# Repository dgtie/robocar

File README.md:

# robocar
stm32f103c8t6

## Setup SD card
[Download Raspberry Pi Zero WH image](https://polyuit-my.sharepoint.com/:u:/g/personal/ensylam_polyu_edu_hk/EfPde7mzcR5NiaSuWeZethsBixlZN2U6amez3VQq-VrPfw?e=RhzQuq)\
Write image to SD card. (using balenaEtcher or otherwise)\
Disable SD card reader (through device manager) and then enable it again.\
Modify the following files (in "boot" drive):

- wpa_supplicant.conf (ssid, password)
- hostname & hosts (raspberrypi -> newHostname, eg 19xxxxxxd)

Put SD card to raspberry pi zero and boot.

## SSH to raspberry pi
launch command prompt\
enter "ping -4 19xxxxxxd.local" to check ip address (Bonjour Print Service)\
SSH via putty or otherwise. (ssh pi@19xxxxxxd.local) (pwd = raspberry)

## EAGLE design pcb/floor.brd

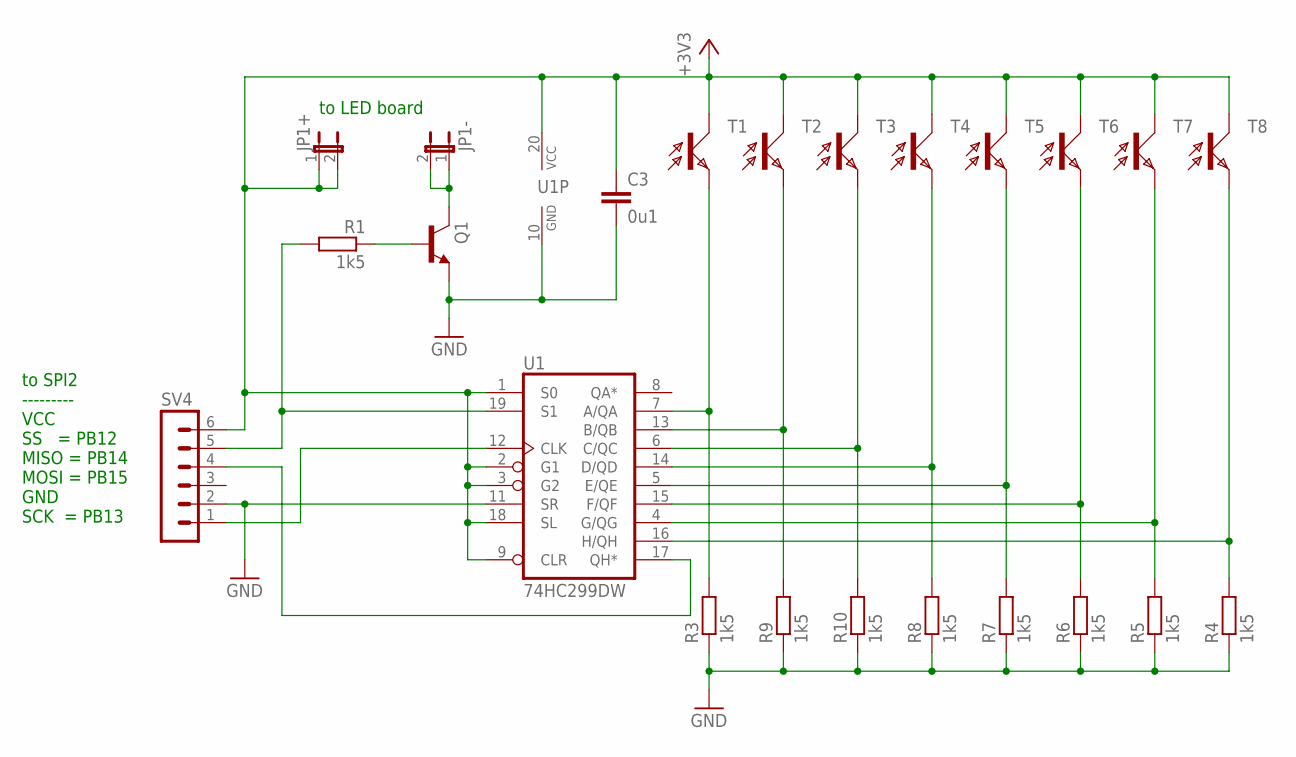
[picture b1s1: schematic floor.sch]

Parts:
C3: 0u1; C0805
JP1+, JP1-: JP1E; JP1
Q1: BC817-25SMD; SOT23-BEC
R1, R3, R4, R5, R6, R7, R8, R9, R10: 1k5; M0805
SV4: MA06-1
T1, T2, T3, T4, T5, T6, T7, T8: PT17-21B; CHIPLED_0805
U1: 74HC299DW; SO20W

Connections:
+3V3: C3.1, JP1+.1, JP1+.2, SV4.6, T1.C, T2.C, T3.C, T4.C, T5.C, T6.C, T7.C, T8.C, U1.1 (S0), U1.2 (G1), U1.3 (G2), U1.9 (CLR), U1.18 (SL), U1.20 (VCC)
GND: C3.2, Q1.E, R3.1, R4.1, R5.1, R6.1, R7.1, R8.1, R9.1, R10.1, SV4.2, U1.10 (GND), U1.11 (SR)
unnamed: R3.2, T1.A (E), U1.7 (A/QA)
unnamed: JP1-.1, JP1-.2, Q1.C
unnamed: R4.2, T8.A (E), U1.16 (H/QH)
unnamed: R9.2, T2.A (E), U1.13 (B/QB)
unnamed: R10.2, T3.A (E), U1.6 (C/QC)
unnamed: R8.2, T4.A (E), U1.14 (D/QD)
unnamed: R7.2, T5.A (E), U1.5 (E/QE)
unnamed: R6.2, T6.A (E), U1.15 (F/QF)
unnamed: R5.2, T7.A (E), U1.4 (G/QG)
unnamed: SV4.1, U1.12 (CLK)
unnamed: SV4.4, U1.17 (QH*)
unnamed: R1.2, SV4.5, U1.19 (S1)
unnamed: Q1.B, R1.1

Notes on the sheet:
to SPI2 --------- VCC SS = PB12 MISO = PB14 MOSI = PB15 GND SCK = PB13
to LED board

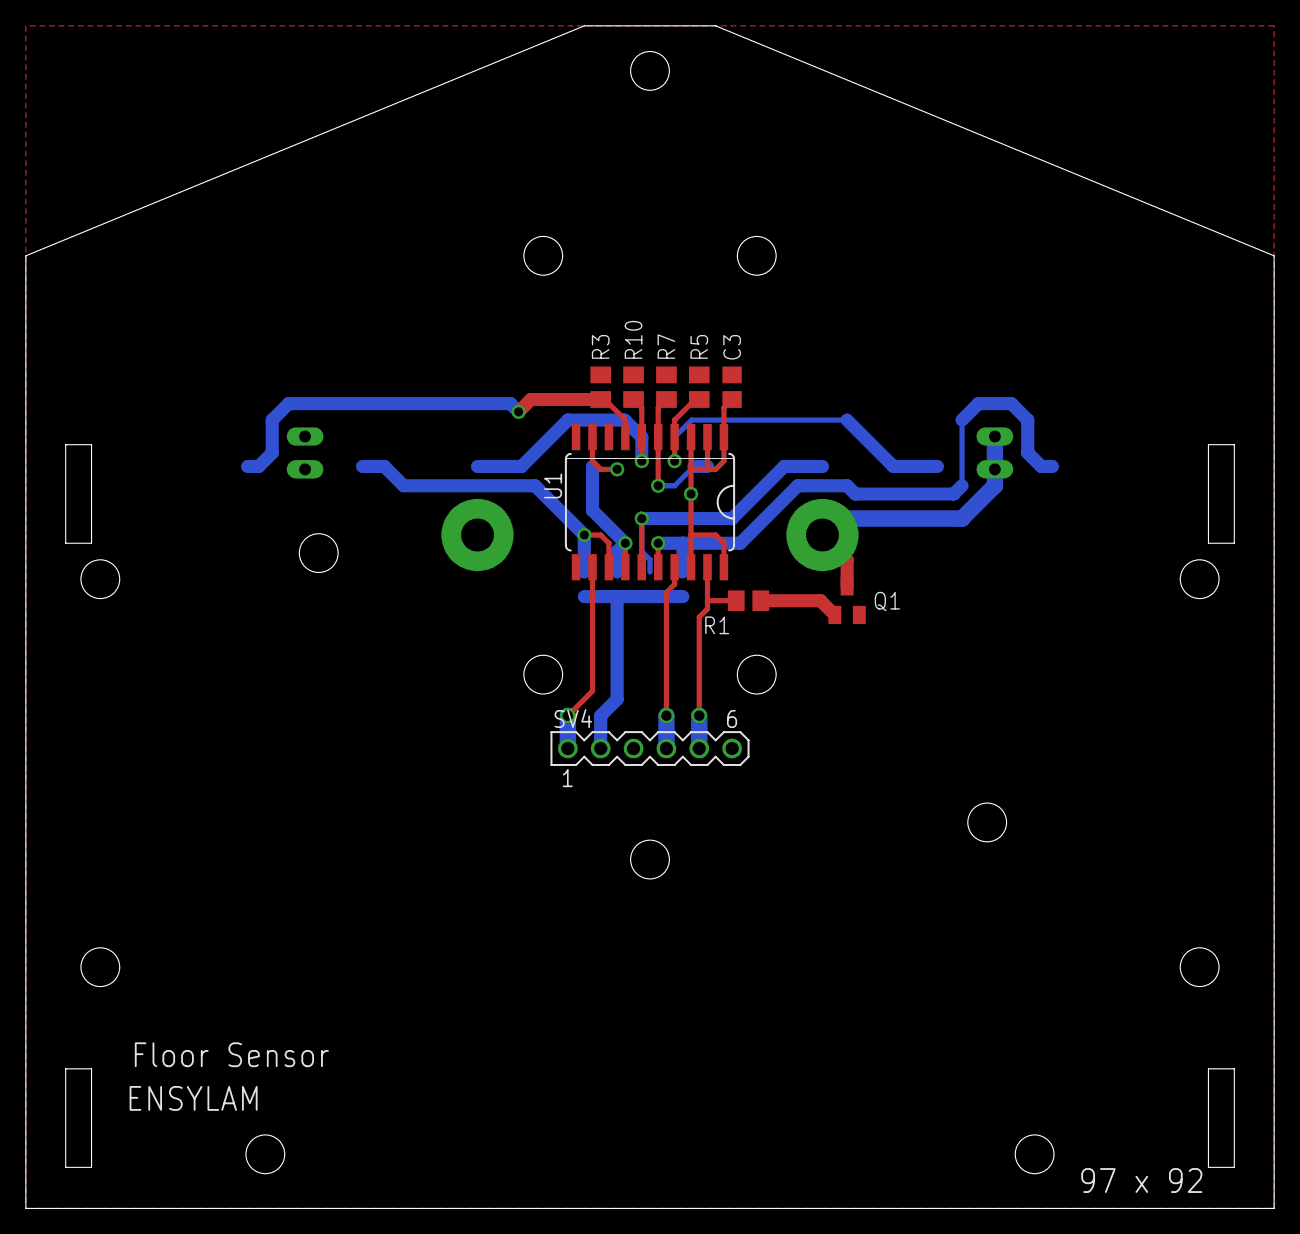
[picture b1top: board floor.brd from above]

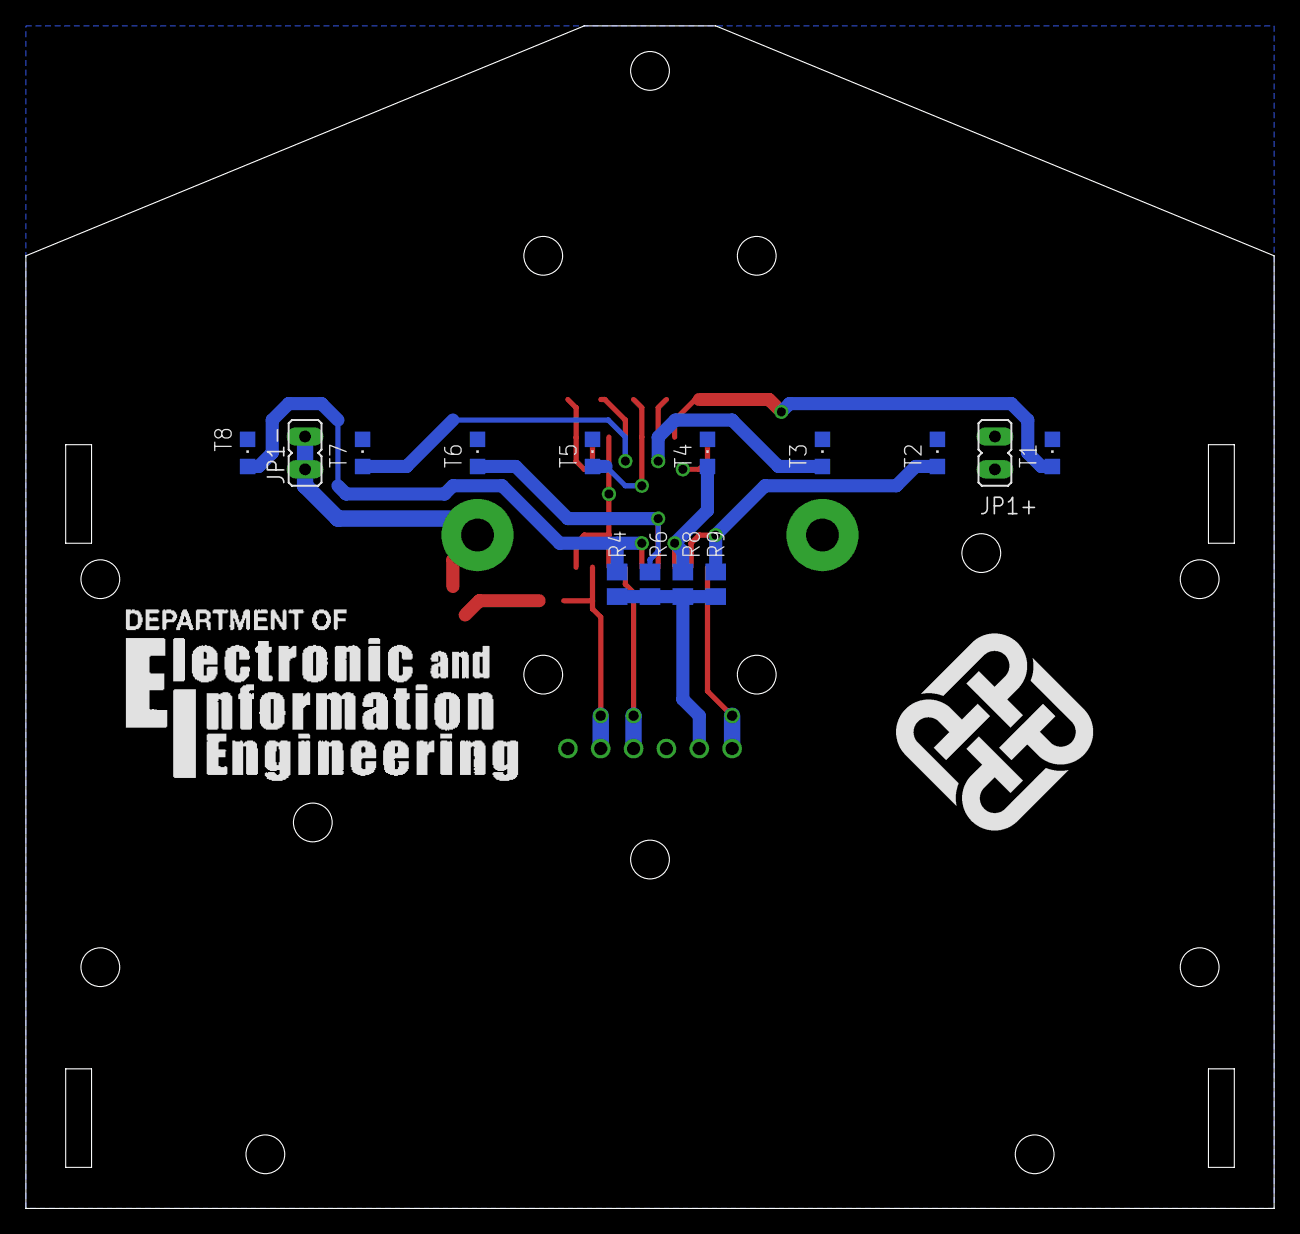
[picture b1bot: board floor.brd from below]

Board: 2 copper layers, 96.5 x 91.4 mm, 25 parts (16 on the bottom side), 15 nets.

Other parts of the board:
U$1: EIE
U$2: POLYU

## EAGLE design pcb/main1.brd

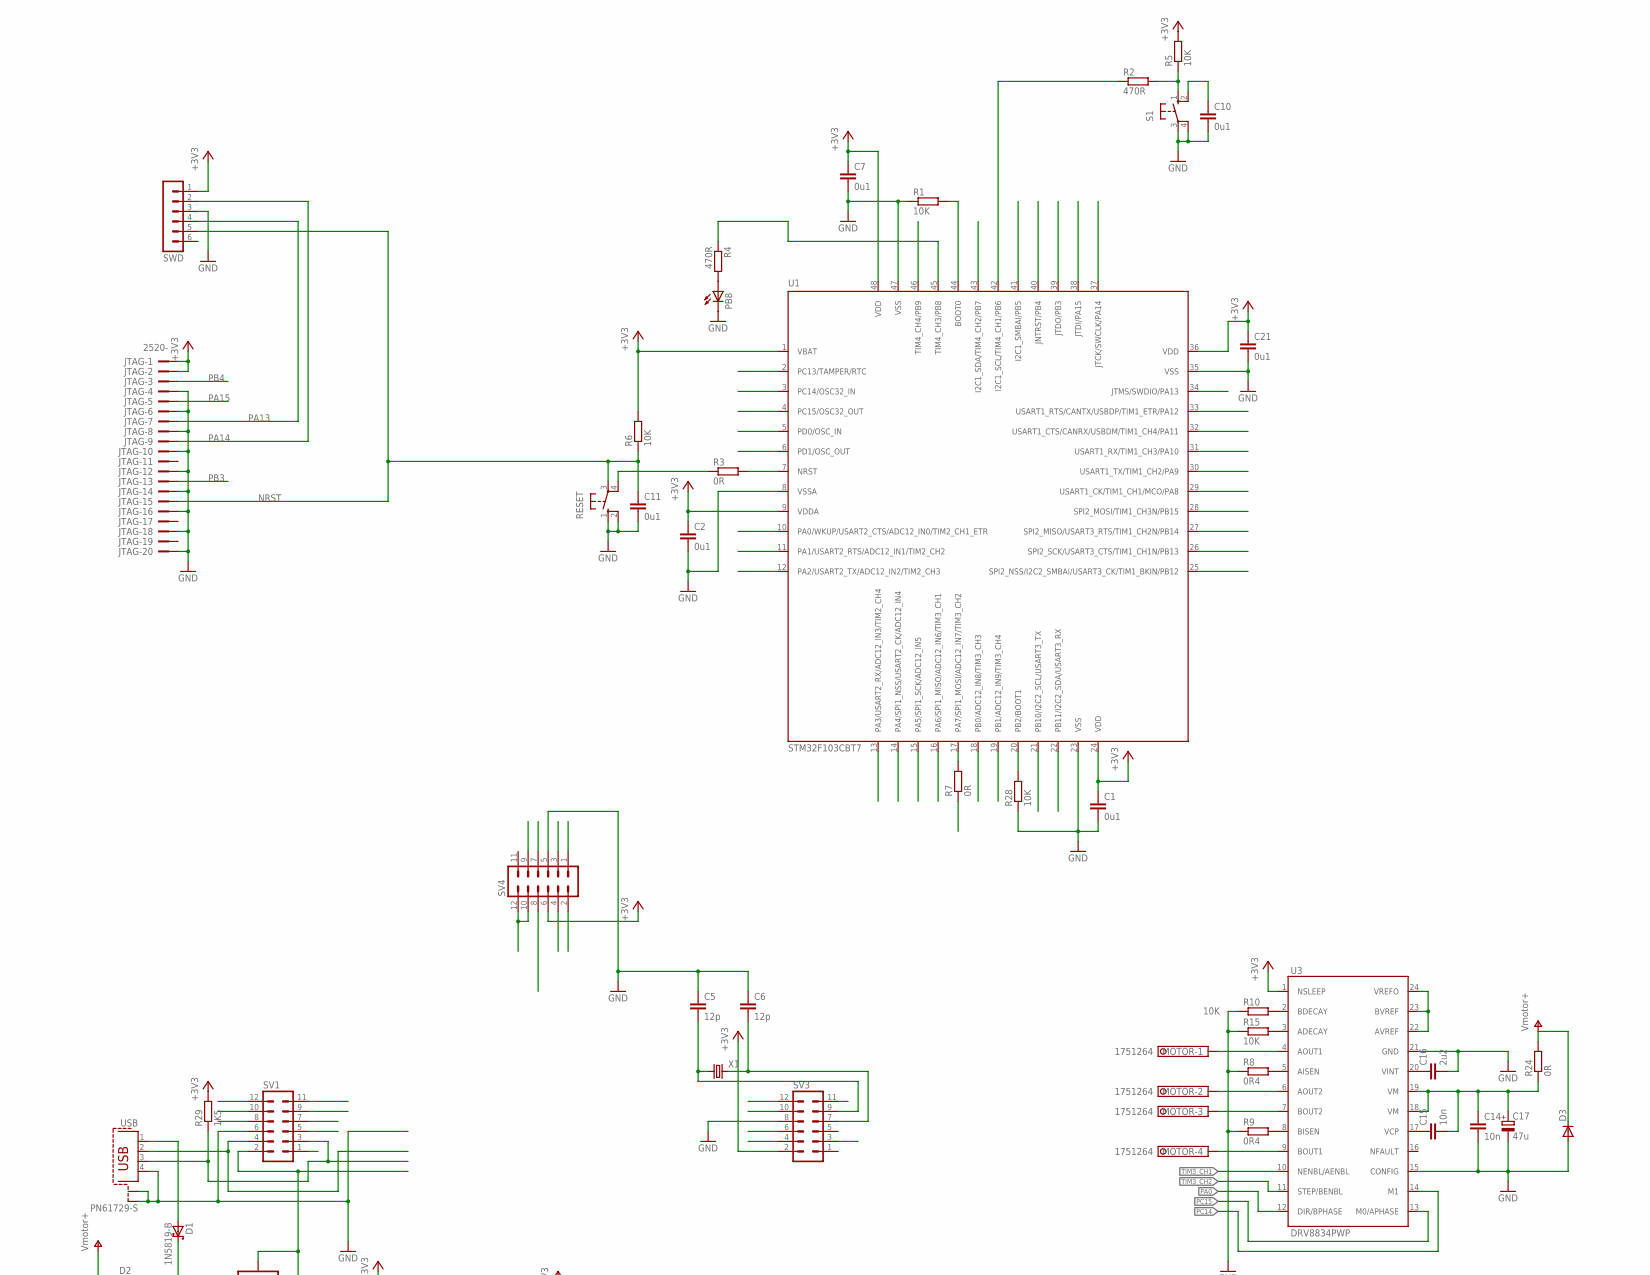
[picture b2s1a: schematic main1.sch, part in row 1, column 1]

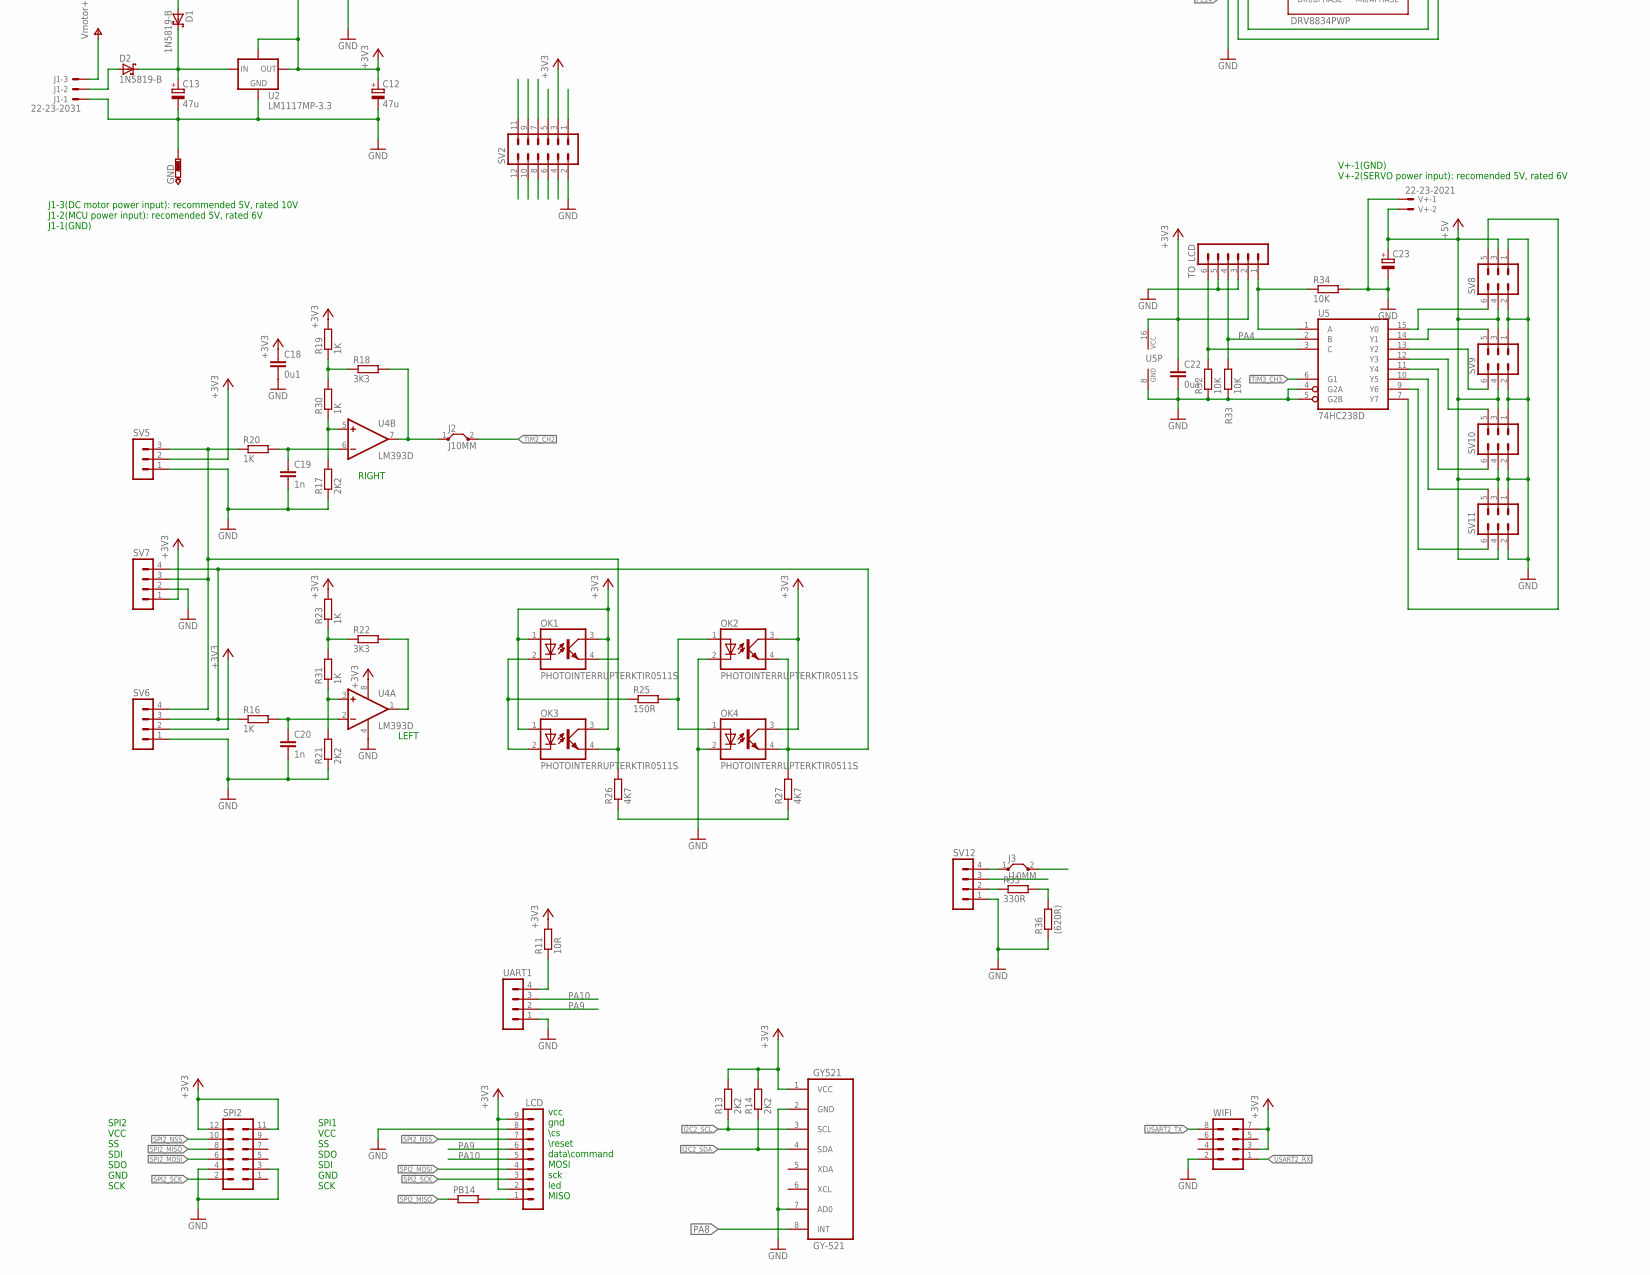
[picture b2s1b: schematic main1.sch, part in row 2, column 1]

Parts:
C1, C2, C7, C10, C11, C18, C21, C22: 0u1; C0805
C5, C6: 12p; C0805
C12, C13, C17: 47u; E1,8-4
C14, C15: 10n; C0805
C16: 2u2; C0805
C19, C20: 1n; C0805
C23: CPOL-EUE2.5-7; E2,5-7
D1, D2: 1N5819-B; DO41-7.6
D3: DIODE-SMB; SMB
GND: PTR1PAD1-13; P1-13
GY521: GY-521
J1: 22-23-2031
J2, J3: J10MM; 10
JTAG: 2520-; PAK100/2500-20
LCD: MA09-1
MOTOR: 1751264
OK1, OK2, OK3, OK4: PHOTOINTERRUPTERKTIR0511S; KTIR0511S
PB8: LED3MM
PB14: R-EU_0207/10; 0207/10
R1, R6, R28, R32, R33, R34: 10K; M0805
R2, R4: 470R; 0207/10
R3, R7, R24: 0R; 0207/10
R5: 10K; 0207/10
R8, R9: 0R4; R2010
R10, R15: 10K; R0805
R11: 10R; M0805
R13, R14, R17, R21: 2K2; M0805
R16, R20: 1K; 0207/10
R18, R22: 3K3; M0805
R19, R23, R30, R31: 1K; M0805
R25: 150R; 0207/10
R26, R27: 4K7; M0805
R29: 1K5; M0805
R35: 330R; M0805
R36: (620R); M0805
RESET: 10-XX; B3F-10XX
S1: 10-XX; B3F-10XX
SPI2: MA06-2
SV1, SV2, SV3, SV4: MA06-2
SV5: MA03-1
SV6, SV7, SV12: MA04-1
SV8, SV9, SV10, SV11: MA03-2
SWD: MA06-1
TO_LCD: MA06-1
U1: STM32F103CBT7; LQFP48-7X7
U2: LM1117MP-3.3; SOT230P700X180-4N
U3: DRV8834PWP; PWP-TSSOP24
U4: LM393D; SO08
U5: 74HC238D; SO16
UART1: MA04-1
USB: PN61729-S
V+: 22-23-2021
WIFI: MA04-2
X1: CRYSTALHC49S; HC49/S

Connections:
+3V3: C1.1, C2.1, C7.1, C12.+, C18.1, C21.1, C22.1, GY521.1 (VCC), JTAG.1, JTAG.2, LCD.2, LCD.9, OK1.1 (A), OK1.3 (COL), OK2.3 (COL), OK3.1 (A), OK3.3 (COL), OK4.3 (COL), R5.2, R6.2, R11.2, R13.2, R14.2, R19.2, R23.2, R29.2, SPI2.11, SPI2.12, SV1.2, SV2.3, SV3.2, SV4.6, SV5.2, SV6.2, SV7.1, SWD.1, TO_LCD.2, U1.1 (VBAT), U1.9 (VDDA), U1.24 (VDD), U1.36 (VDD), U1.48 (VDD), U2.2 (OUT), U2.4 (TAB), U3.1 (NSLEEP), U4.8 (V+), U5.16 (VCC), WIFI.3, WIFI.7
+5V: C23.+, SV8.3, SV8.4, SV9.3, SV9.4, SV10.3, SV10.4, SV11.3, SV11.4, V+.2
BOOT0: R1.2, SV2.5, U1.44 (BOOT0)
BOOT1: R28.2, SV4.8, U1.20 (PB2/BOOT1)
GND: C1.2, C2.2, C5.1, C6.1, C7.2, C10.2, C11.2, C12.-, C13.-, C14.2, C16.2, C17.-, C18.2, C19.2, C20.2, C21.2, C22.2, C23.-, D3.A, GND.TP, GY521.2 (GND), GY521.7 (AD0), J1.1, JTAG.4, JTAG.6, JTAG.8, JTAG.10, JTAG.12, JTAG.14, JTAG.16, JTAG.18, JTAG.20, LCD.8, OK2.2 (C), OK4.2 (C), PB8.K (C), R1.1, R8.1, R9.1, R10.1, R15.1, R17.1, R21.1, R26.1, R27.1, R28.1, R32.1, R33.1, R34.2, R36.1, RESET.1 (S), RESET.2 (S1), S1.3, S1.4 (P1), SPI2.3, SPI2.4, SV1.6, SV2.2, SV3.8, SV4.5, SV5.1, SV6.1, SV7.2, SV8.1, SV8.2, SV9.1, SV9.2, SV10.1, SV10.2, SV11.1, SV11.2, SV12.1, SWD.3, TO_LCD.3, TO_LCD.5, U1.8 (VSSA), U1.23 (VSS), U1.35 (VSS), U1.47 (VSS), U2.1 (GND), U3.15 (CONFIG), U3.21 (GND), U3.EXP (GND), U4.4 (V-), U5.4 (G2A), U5.5 (G2B), U5.8 (GND), UART1.1, USB.4, USB.S1, USB.S2, V+.1, WIFI.2
I2C2_SCL: GY521.3 (SCL), R13.1, SV4.9, U1.21 (PB10/I2C2_SCL/USART3_TX)
I2C2_SDA: GY521.4 (SDA), R14.1, SV4.10, SV4.12, U1.22 (PB11/I2C2_SDA/USART3_RX)
unnamed: OK1.4 (EMIT), OK3.4 (EMIT), R20.1, R26.2, SV5.3, SV6.4, SV7.3
unnamed: D1.A, USB.1
unnamed: J3.1, SV12.4
unnamed: R11.1, UART1.4
unnamed: R3.2, U1.7 (NRST)
unnamed: OK1.2 (C), OK3.2 (C), R25.1
unnamed: R18.1, R19.1, R30.2
unnamed: R22.1, R23.1, R31.2
unnamed: LCD.1, PB14.2
unnamed: OK2.1 (A), OK4.1 (A), R25.2
unnamed: R3.1, RESET.4 (P1)
unnamed: OK2.4 (EMIT), OK4.4 (EMIT), R16.1, R27.2, SV6.3, SV7.4
unnamed: D2.A, J1.2, J3.2
unnamed: SV8.6, U5.15 (Y0)
unnamed: SV9.5, U5.14 (Y1)
unnamed: SV9.6, U5.13 (Y2)
unnamed: SV10.5, U5.12 (Y3)
unnamed: SV10.6, U5.11 (Y4)
unnamed: C19.1, R20.2, U4.6 (-IN)
unnamed: R2.2, R5.1, S1.1 (S)
unnamed: C10.1, S1.2 (S1)
unnamed: SV11.5, U5.10 (Y5)
unnamed: SV11.6, U5.9 (Y6)
unnamed: SV8.5, U5.7 (Y7)
unnamed: C13.+, D1.C, D2.C, U2.3 (IN)
unnamed: PB8.A, R4.2
unnamed: R7.2, U1.17 (PA7/SPI1_MOSI/ADC12_IN7/TIM3_CH2)
unnamed: R35.1, SV12.2
unnamed: R8.2, U3.5 (AISEN)
unnamed: R9.2, U3.8 (BISEN)
unnamed: R10.2, U3.2 (BDECAY)
unnamed: R15.2, U3.3 (ADECAY)
unnamed: U3.22 (AVREF), U3.23 (BVREF), U3.24 (VREFO)
unnamed: C15.1, U3.17 (VCP)
unnamed: C16.1, U3.20 (VINT)
unnamed: R17.2, R30.1, U4.5 (+IN)
unnamed: C20.1, R16.2, U4.2 (-IN)
unnamed: R21.2, R31.1, U4.3 (+IN)
unnamed: C14.1, C15.2, C17.+, R24.1, U3.18 (VM), U3.19 (VM)
NRST: C11.1, JTAG.15, R6.1, RESET.3, SWD.5
PA0: SV3.10, U1.10 (PA0/WKUP/USART2_CTS/ADC12_IN0/TIM2_CH1_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), U3.12 (DIR/BPHASE)
PA4: R33.2, SV4.1, TO_LCD.4, U1.14 (PA4/SPI1_NSS/USART2_CK/ADC12_IN4), U5.2 (B)
PA5: SV4.2, U1.15 (PA5/SPI1_SCK/ADC12_IN5)
PA8: GY521.8 (INT), SV1.7, U1.29 (USART1_CK/TIM1_CH1/MCO/PA8)
PA9: LCD.6, SV1.8, U1.30 (USART1_TX/TIM1_CH2/PA9), UART1.2
PA10: LCD.5, SV1.5, U1.31 (USART1_RX/TIM1_CH3/PA10), UART1.3
PA13: JTAG.7, SV1.1, SWD.4, U1.34 (JTMS/SWDIO/PA13)
PA14: JTAG.9, SV2.12, SWD.2, U1.37 (JTCK/SWCLK/PA14)
PA15: JTAG.5, SV2.11, U1.38 (JTDI/PA15)
PB1: SV4.7, U1.19 (PB1/ADC12_IN9/TIM3_CH4)
PB3: JTAG.13, SV2.10, U1.39 (JTDO/PB3)
PB4: JTAG.3, R35.2, R36.2, SV2.9, U1.40 (JNTRST/PB4)
PB5: SV2.8, SV12.3, U1.41 (I2C1_SMBAI/PB5)
PB6: R2.1, SV2.7, U1.42 (I2C1_SCL/TIM4_CH1/PB6)
PB7: R22.2, SV2.6, U1.43 (I2C1_SDA/TIM4_CH2/PB7), U4.1 (OUT)
PB8: R4.1, SV2.4, U1.45 (TIM4_CH3/PB8)
PC13: SV3.4, U1.2 (PC13/TAMPER/RTC)
PC14: SV3.3, U1.3 (PC14/OSC32_IN), U3.14 (M1)
PC15: SV3.6, U1.4 (PC15/OSC32_OUT), U3.13 (M0/APHASE)
PD0: C6.2, SV3.7, U1.5 (PD0/OSC_IN), X1.2
PD1: C5.2, SV3.9, U1.6 (PD1/OSC_OUT), X1.1
SPI2_MISO: PB14.1, SPI2.8, SV1.9, U1.27 (SPI2_MISO/USART3_RTS/TIM1_CH2N/PB14)
SPI2_MOSI: LCD.4, SPI2.6, SV1.10, U1.28 (SPI2_MOSI/TIM1_CH3N/PB15)
SPI2_NSS: LCD.7, SPI2.10, SV1.11, U1.25 (SPI2_NSS/I2C2_SMBAI/USART3_CK/TIM1_BKIN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)
SPI2_SCK: LCD.3, SPI2.2, SV1.12, U1.26 (SPI2_SCK/USART3_CTS/TIM1_CH1N/PB13)
TIM2_CH2: J2.2, SV3.12, U1.11 (PA1/USART2_RTS/ADC12_IN1/TIM2_CH2)
TIM2_CH2A: J2.1, R18.2, U4.7 (OUT)
TIM3_CH1: SV4.3, U1.16 (PA6/SPI1_MISO/ADC12_IN6/TIM3_CH1), U3.10 (NENBL/AENBL)
TIM3_CH2: R7.1, SV3.11, U3.11 (STEP/BENBL)
TIM3_CH3: SV4.4, U1.18 (PB0/ADC12_IN8/TIM3_CH3), U5.6 (G1)
TIM4_CH4: SV2.1, U1.46 (TIM4_CH4/PB9)
U5A: R34.1, TO_LCD.1, U5.1 (A)
U5C: R32.2, TO_LCD.6, U5.3 (C)
USART2_RX: U1.13 (PA3/USART2_RX/ADC12_IN3/TIM2_CH4), WIFI.1
USART2_TX: U1.12 (PA2/USART2_TX/ADC12_IN2/TIM2_CH3), WIFI.8
USBDM: SV1.4, U1.32 (USART1_CTS/CANRX/USBDM/TIM1_CH4/PA11), USB.2
USBDP: R29.1, SV1.3, U1.33 (USART1_RTS/CANTX/USBDP/TIM1_ETR/PA12), USB.3
V+: D3.C, J1.3, R24.2
X21: MOTOR.4, U3.9 (BOUT1)
X22: MOTOR.3, U3.7 (BOUT2)
X23: MOTOR.2, U3.6 (AOUT2)
X24: MOTOR.1, U3.4 (AOUT1)

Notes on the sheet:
SPI2 VCC SS SDI SDO GND SCK
vcc gnd \cs \reset data\command MOSI sck led MISO
RIGHT
LEFT
SPI1 VCC SS SDO SDI GND SCK
J1-3(DC motor power input): recommended 5V, rated 10V J1-2(MCU power input): recomended 5V, rated 6V J1-1(GND)
V+-1(GND) V+-2(SERVO power input): recomended 5V, rated 6V

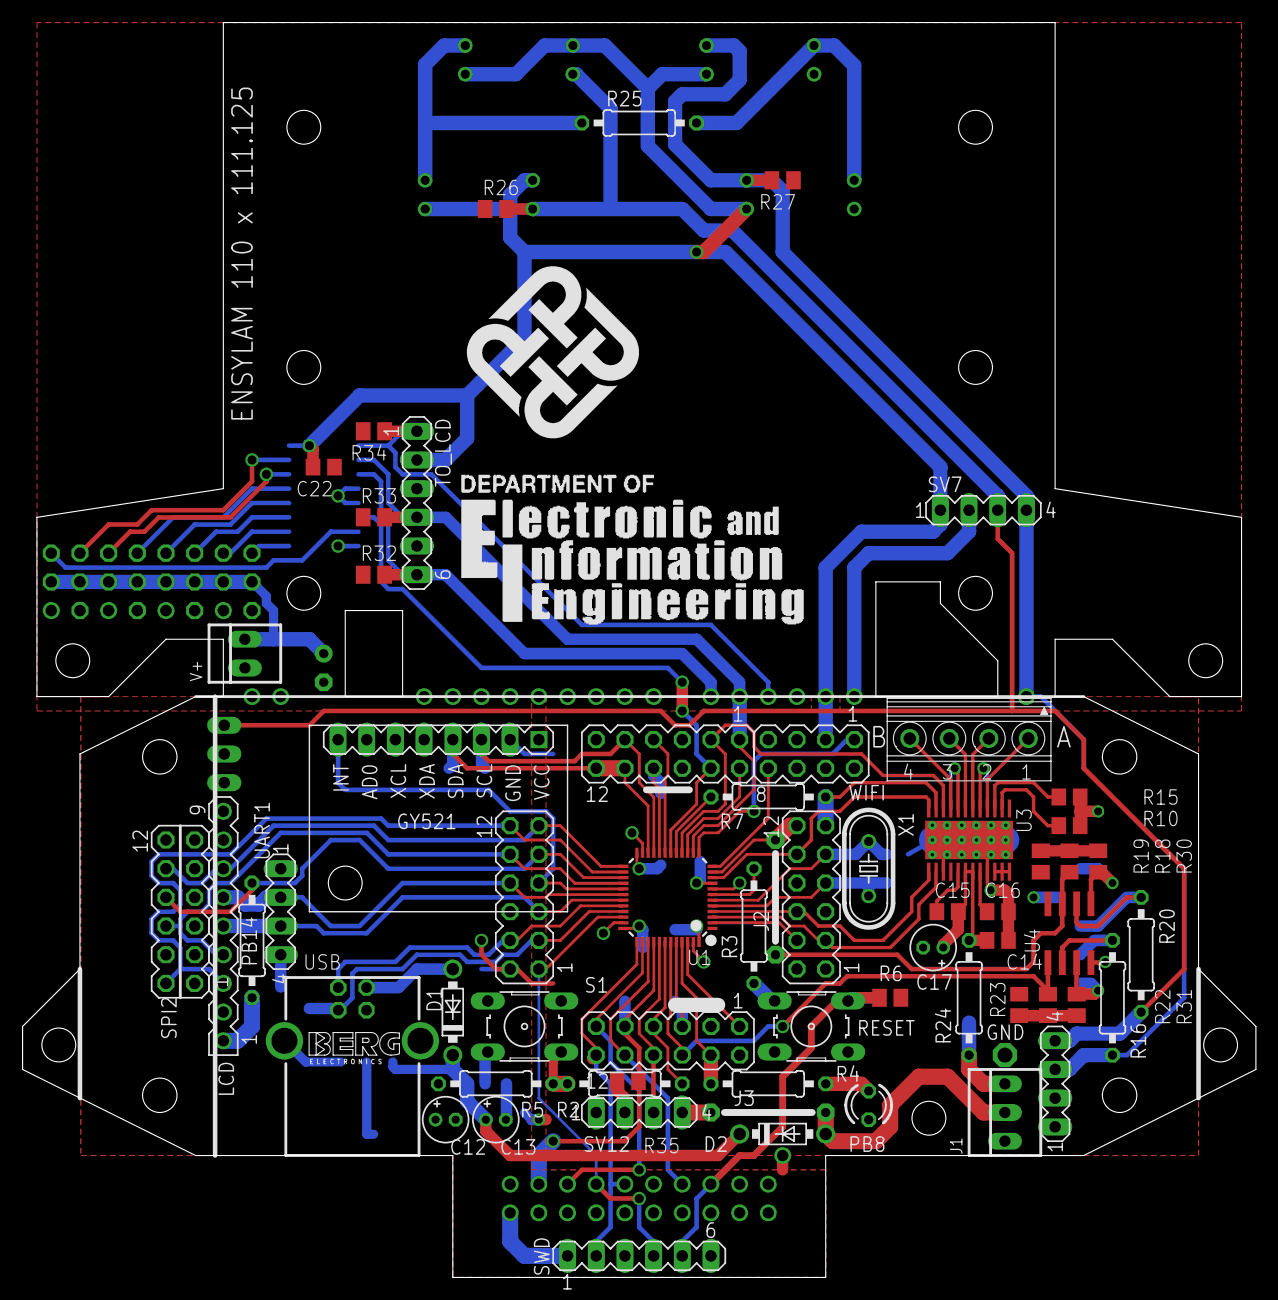
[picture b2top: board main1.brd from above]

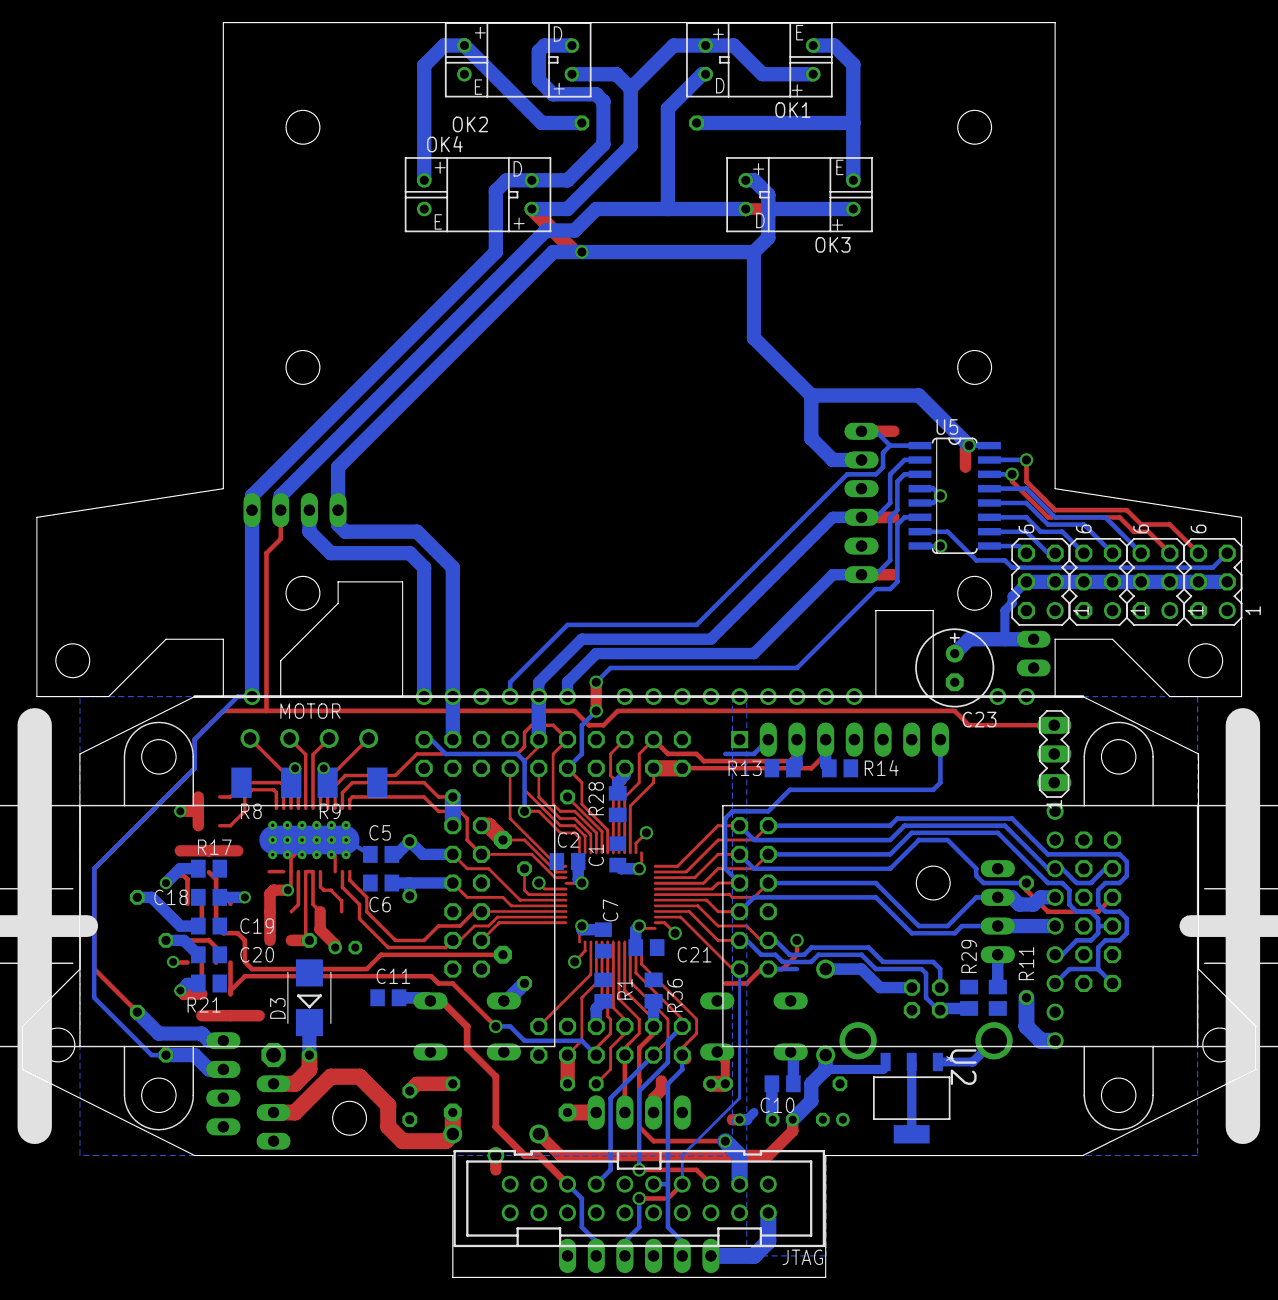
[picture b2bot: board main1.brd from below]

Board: 2 copper layers, 109.2 x 111.1 mm, 102 parts (38 on the bottom side), 89 nets.

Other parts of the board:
U$1: POLYU
U$2: EIE
U$5, U$6: 70103

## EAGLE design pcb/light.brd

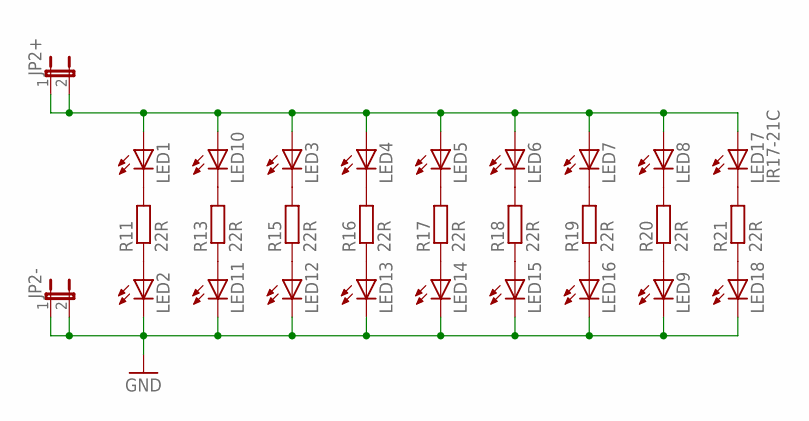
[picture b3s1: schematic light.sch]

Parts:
JP2+, JP2-: JP1E; JP1
LED1, LED2, LED3, LED4, LED5, LED6, LED7, LED8, LED9, LED10, LED11, LED12, LED13, LED14, LED15, LED16, LED18: LEDCHIPLED_0805; CHIPLED_0805
LED17: IR17-21C; CHIPLED_0805
R11, R13, R15, R16, R17, R18, R19, R20, R21: 22R; M0805

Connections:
+3V3: JP2+.1, JP2+.2, LED1.A, LED3.A, LED4.A, LED5.A, LED6.A, LED7.A, LED8.A, LED10.A, LED17.A
GND: JP2-.1, JP2-.2, LED2.C, LED9.C, LED11.C, LED12.C, LED13.C, LED14.C, LED15.C, LED16.C, LED18.C
unnamed: LED2.A, R11.1
unnamed: LED1.C, R11.2
unnamed: LED10.C, R13.2
unnamed: LED11.A, R13.1
unnamed: LED3.C, R15.2
unnamed: LED4.C, R16.2
unnamed: LED5.C, R17.2
unnamed: LED6.C, R18.2
unnamed: LED7.C, R19.2
unnamed: LED8.C, R20.2
unnamed: LED9.A, R20.1
unnamed: LED12.A, R15.1
unnamed: LED13.A, R16.1
unnamed: LED14.A, R17.1
unnamed: LED15.A, R18.1
unnamed: LED16.A, R19.1
unnamed: LED18.A, R21.1
unnamed: LED17.C, R21.2

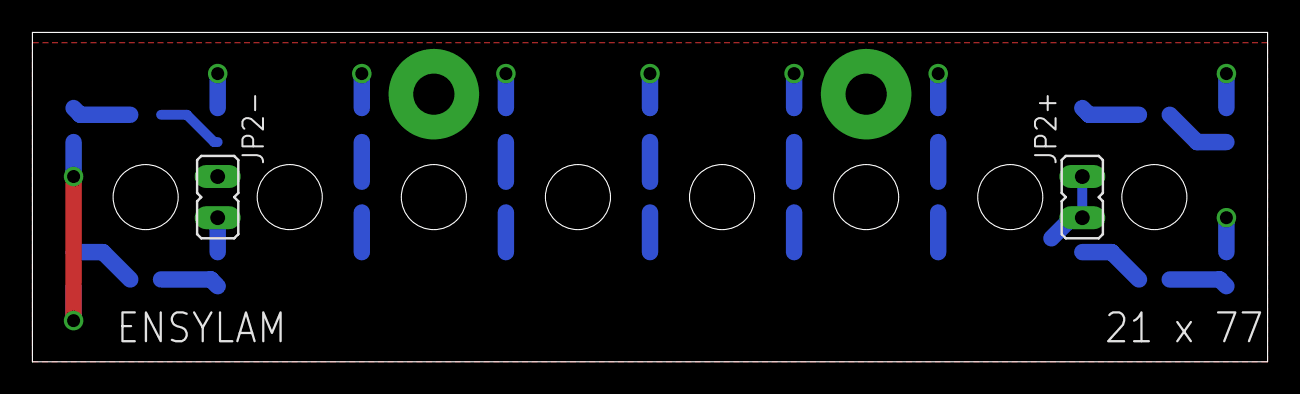
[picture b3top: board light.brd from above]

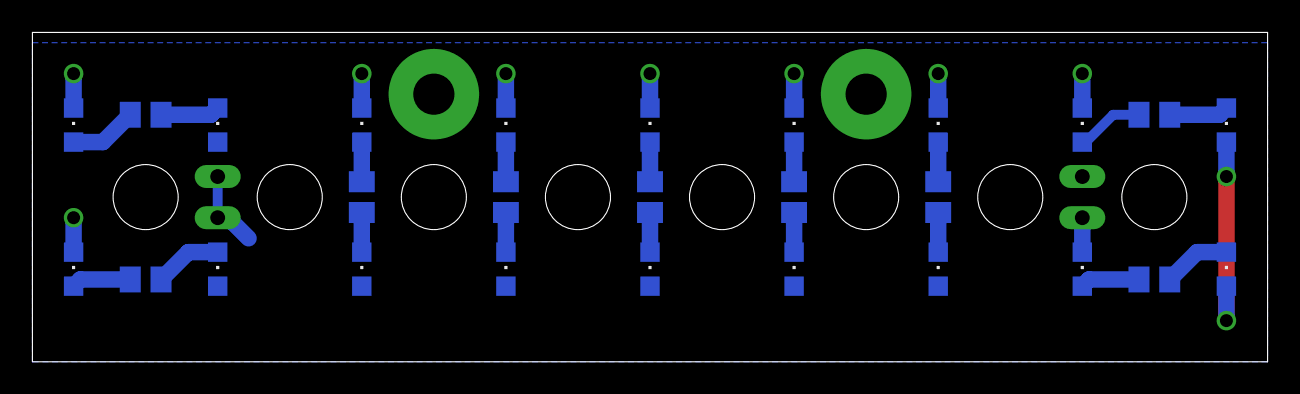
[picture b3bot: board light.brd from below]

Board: 2 copper layers, 76.2 x 20.3 mm, 29 parts (27 on the bottom side), 20 nets.

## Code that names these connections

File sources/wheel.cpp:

#include <stm32f10x.h>
#include <lamos.h>
#include "wheel.h"

/*
PA1 = TIM2_CH2, PB7 = TIM4_CH2

PA6 = TIM3_CH1 = AENBL
PA7 = TIM3_CH2 = BENBL
PA0 = BPHASE
PC15 = APHASE
PC14 = M1

PB12 = IR LED / MODE
PB13 = SPI2_SCK
PB14 = SPI2_MISO
PB15 = SPI2_MOSI
*/

#define PERIOD 44999	// period = 2.5 ms (400 Hz)

void __attribute__((weak)) wheel(wheel_struct &p) { p.left = p.right = 0; }

namespace
{

wheel_mode mode = FORWARD;

}

void wheel(wheel_mode m) {
  switch (mode = m) {
  case FORWARD:
    GPIOA->BRR = 1; GPIOC->BRR = 0x8000;
    break;
  case BACKWARD:
    GPIOA->BSRR = 1; GPIOC->BSRR = 0x8000;
    break;
  case LEFT:
    GPIOA->BSRR = 1; GPIOC->BRR = 0x8000;
    break;
  case RIGHT:
    GPIOA->BRR = 1; GPIOC->BSRR = 0x8000;
    break;
  default:;
  }
}

namespace
{

wheel_struct val;
struct {unsigned short left, right;} last, current;

SERVICE constructor(void) {
  RCC->APB1ENR |= RCC_APB1ENR_TIM2EN | RCC_APB1ENR_TIM3EN | RCC_APB1ENR_TIM4EN;
  TIM3->PSC = 3;			// 72/4 = 18 MHz
  TIM3->ARR = PERIOD;
  TIM2->SMCR = TIM4->SMCR = 0x67;	// TI2FP2
  TIM2->CCMR1 |= 0x100;			// CC2 as input, IC2 mapped on TI2
  TIM4->CCMR1 |= 0x100;
  TIM2->CR1 |= TIM_CR1_CEN;
  TIM4->CR1 |= TIM_CR1_CEN;

  RCC->APB2ENR |= RCC_APB2ENR_IOPAEN | RCC_APB2ENR_IOPCEN;
  int
  i = GPIOA->CRL & 0x00fffff0;		// select PA7, PA6, & PA0
  GPIOA->CRL = i | 0xaa000002;		// a = AFPP, 2 = PP(2MHz)
  i = GPIOC->CRH & 0x00ffffff;		// select PC15 & PC14
  GPIOC->CRH = i | 0x22000000;		// 2 = PP(2MHz)
  TIM3->CCMR1 = 0x6868;				// ch2 & ch1: PWM1, preload
  TIM3->CCER = TIM_CCER_CC2E | TIM_CCER_CC1E;	// OC output enable

  RCC->APB2ENR |= RCC_APB2ENR_IOPBEN;		// enable clock for PORTB
  i = GPIOB->CRH & 0xff00ffff;			// select PB13, PB12
  GPIOB->CRH = i | 0x00a20000;			// a = AFPP, 2 = PP 2MHz
  RCC->APB1ENR |= RCC_APB1ENR_SPI2EN;		// power up SPI2
  SPI2->CR2 |= SPI_CR2_RXNEIE;
  SPI2->CR1 = SPI_CR1_CPHA | SPI_CR1_CPOL | SPI_CR1_MSTR | SPI_CR1_BR |
              SPI_CR1_SSM | SPI_CR1_SSI;
						// 36 MHz / 256 = 140.625 kHz
  SPI2->CR1 |= SPI_CR1_SPE;

  TIM3->CR1 |= TIM_CR1_CEN;		// turn on timer
  TIM3->SR &= ~TIM_SR_UIF;		// clear UIF
  TIM3->DIER |= TIM_DIER_UIE;		// update interrupt enable
  NVIC_EnableIRQ(TIM3_IRQn);

  last.right = TIM2->CNT;
  last.left = TIM4->CNT;

  return [](Service&) {
    if (mode == STOP) { TIM3->CCR1 = TIM3->CCR2 = 0; return; }
    val.left = current.left - last.left; last.left = current.left;
    val.right = current.right - last.right; last.right = current.right;
    wheel(val);
    TIM3->CCR2 = val.left > PERIOD ? PERIOD : val.left;
    TIM3->CCR1 = val.right > PERIOD ? PERIOD : val.right;
  };
}

Service _wheel(constructor());

}

extern "C"
{

void TIM3_IRQHandler(void) {
  current.right = TIM2->CNT;
  current.left = TIM4->CNT;
  val.floor = 0xffffffff;
  GPIOB->BSRR = 0x1000;			// IR LED ON, MODE = parallel load
  SPI2->DR = 0;
  NVIC_EnableIRQ(SPI2_IRQn);
  TIM3->SR &= ~TIM_SR_UIF;
}

void SPI2_IRQHandler(void) {
  char *c = (char*)&val.floor;
  *c = SPI2->DR;
  if (GPIOB->ODR & 0x1000) {
    if (!(val.floor>>=8)) GPIOB->BRR = 0x1000;
    SPI2->DR = 0;
  } else {
    NVIC_DisableIRQ(SPI2_IRQn);
    _wheel.append(0);
  }
}

}

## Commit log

2019-06-10 Create temp
